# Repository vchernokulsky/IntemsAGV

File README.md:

#ROS
В репозитории находятся два рабочих пространства:

- рабочее пространства робота (для jetson nano):
`IntemsAGV/software/catkin_ws`
- рабочее пространство с симуляциями в Gazebo
`IntemsAGV/software/Simulation/catkin_ws`

Для работы с Ros в каждом терминале, находясь в корне рабочего пространства
(папка catkin_ws) необходимо выполнить команду `source devel/setup.bash`

Для распределенного запуска нод в каждом терминале необходимо указать адрес 
Ros-мастера(jetson nano, порт 11311 является стандартным): `export ROS_MASTER_URI=http://192.168.0.150:11311` 

## Custom diff drive
Управление роботом написаное нами

- осуществляет отправку данных полученных из топика /cmd_vel на робота в формате [left_dir, left_speed, right_dir,right_speed]
- на основе данных считанных с энкодера (**линейные скорости** левого и правого колеса) публикует одометрию
- публикует tf состояние робота
- публикует данные с rplidar (LaserScan) в топик /scan
- ~~публикует данные с raspbery-cam~~

Для запуска: `roslaunch cube_robot cube_robot.launch`

## diff_drive (Python)
Сделано на основе https://github.com/merose/diff_drive

- осуществляет отправку данных полученных из топика /cmd_vel на робота в формате [left_dir, left_speed, right_dir,right_speed]
- на основе данных считанных с энкодера (**кол-во тиков** на левом и правом колесе) публикует одометрию

Настрока параметров роботов осуществляется в файле `IntemsAGV/software/catkin_ws/src/diff_drive/config/params.yaml`

Для запуска: `roslaunch diff_drive diff_drive.launch`

## differential drive (c++)
**!!!требует доработки для использования с нашим роботом!!!**

пока запущен только пример

Для использования необходимо установить ros-control, ros-controllers: 

`sudo apt-get install ros-melodic-ros-control ros-melodic-ros-controllers`

Документация по ros-control: https://github.com/ros-controls/ros_control/wiki

Пример использования https://github.com/eborghi10/my_ROS_mobile_robot.git 

Для запуска примера: ` roslaunch my_robot_base hw_control.launch`

Конфигурация робота для примера: `IntemsAGV/software/catkin_ws/src/my_ROS_mobile_robot/my_robot_control/config`

- на основе /cmd_vel вычисляет линейные скорости для левого и правого колеса и публикует в топики /my_robot/right_wheel_vel и /my_robot/left_wheel_vel
- (_может быть изменено_) публикует одометрию на основе на основе угла поворота колёс (угол поворота читается из топиков /my_robot/left_wheel_angle и /my_robot/right_wheel_angle)

## Запуск отельных нод
#### публикация tf состояния робота
`roslaunch cube_robot tf.launch`
#### Rplidar
`roslaunch rplidar_ros rplidar.launch`
#### teleop (из консоли)
`roslaunch cube_robot_teleop cube_robot_teleop_key.launch`
#### teleop (из приложения android)
`roslaunch cube_robot_teleop cube_robot_teleop_server.launch`

установщик для приложения находится в папке `IntemsAGV/software/RobotController/app/release`

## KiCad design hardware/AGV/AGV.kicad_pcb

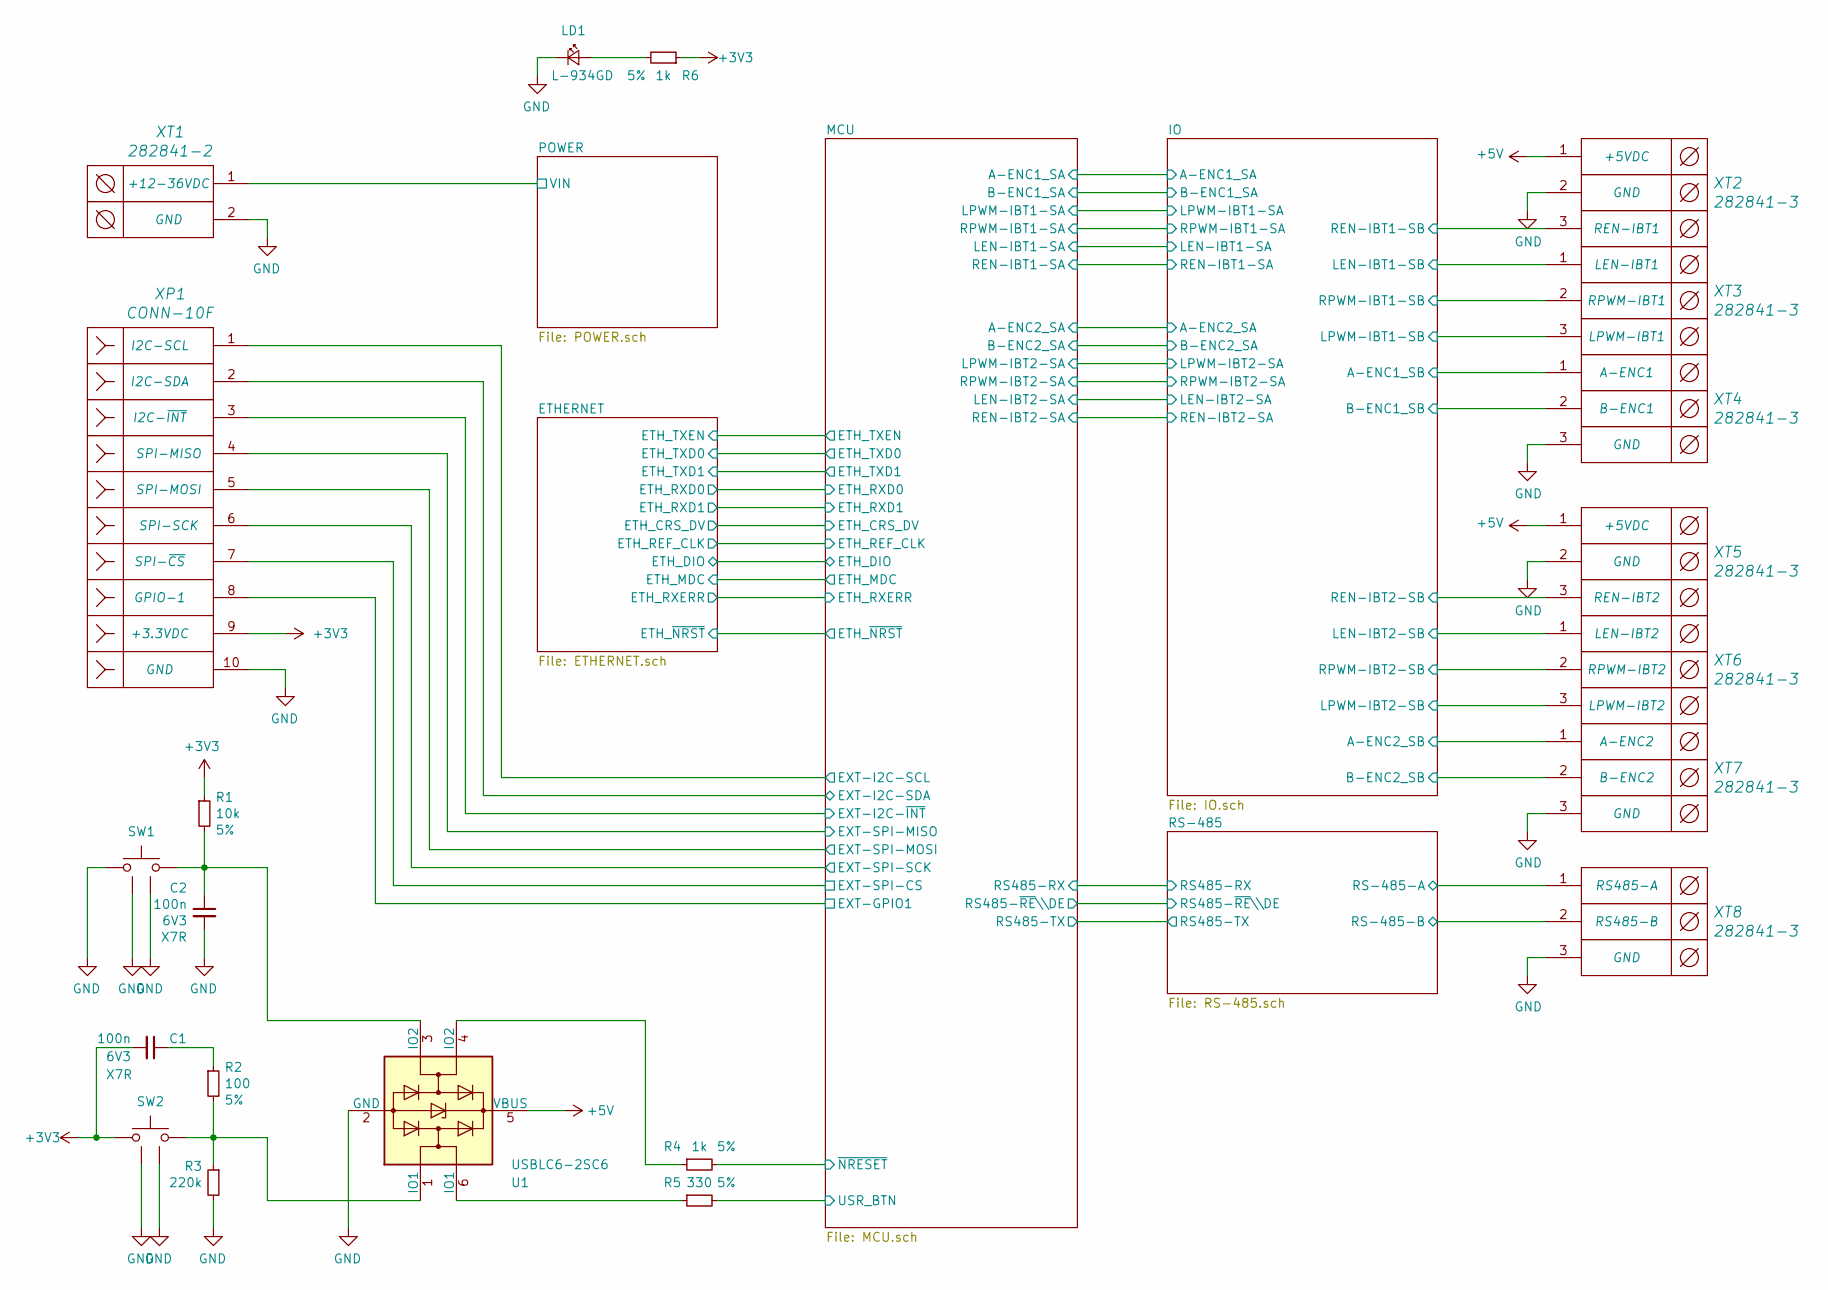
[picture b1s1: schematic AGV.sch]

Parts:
C1, C2: 100n; C_0603_1608Metric; Tolerance X7R; PartNumber CC0603KRX7R9BB104
LD1: L-934GD; LED_D3.0mm; PartNumber L-934GD
R1: 10k; R_0603_1608Metric; Tolerance 5%; PartNumber RC0603FR-0710KL
R2: 100; R_0603_1608Metric; Tolerance 5%; PartNumber RC0603FR-07100RL
R3: 220k; R_0603_1608Metric; Tolerance Tolerance; PartNumber RC0603FR-07200KL
R4, R6: 1k; R_0603_1608Metric; Tolerance 5%; PartNumber CRCW06031K00FKEA
R5: 330; R_0603_1608Metric; Tolerance 5%; PartNumber RC0603FR-07330RL
SW1, SW2: 1-1825027-7; PartNumber 1-1825027-7
U1: USBLC6-2SC6; SOT-23-6; PartNumber USBLC6-2SC6
XP1: CONN-10F; PinSocket_1x10_P2.54mm_Vertical; PartNumber PBS-10
XT1: 282841-2; PartNumber 282841-2
XT2, XT3, XT4, XT5, XT6, XT7, XT8: 282841-3; PartNumber 282841-3

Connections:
+3V3: C1.2, R1.1, R6.1, SW2.2, XP1.9; also elsewhere on the board
+5V: U1.5 (VBUS), XT2.1, XT5.1; also elsewhere on the board
/IO/A-ENC1_SB: XT4.1; also elsewhere on the board
/IO/A-ENC2_SB: XT7.1; also elsewhere on the board
/IO/B-ENC1_SB: XT4.2; also elsewhere on the board
/IO/B-ENC2_SB: XT7.2; also elsewhere on the board
/IO/LEN-IBT1-SB: XT3.1; also elsewhere on the board
/IO/LEN-IBT2-SB: XT6.1; also elsewhere on the board
/IO/LPWM-IBT1-SB: XT3.3; also elsewhere on the board
/IO/LPWM-IBT2-SB: XT6.3; also elsewhere on the board
/IO/REN-IBT1-SB: XT2.3; also elsewhere on the board
/IO/REN-IBT2-SB: XT5.3; also elsewhere on the board
/IO/RPWM-IBT1-SB: XT3.2; also elsewhere on the board
/IO/RPWM-IBT2-SB: XT6.2; also elsewhere on the board
/MCU/EXT-GPIO1: XP1.8; also elsewhere on the board
/MCU/EXT-I2C-SCL: XP1.1; also elsewhere on the board
/MCU/EXT-I2C-SDA: XP1.2; also elsewhere on the board
/MCU/EXT-I2C-~INT: XP1.3; also elsewhere on the board
/MCU/EXT-SPI-CS: XP1.7; also elsewhere on the board
/MCU/EXT-SPI-MISO: XP1.4; also elsewhere on the board
/MCU/EXT-SPI-MOSI: XP1.5; also elsewhere on the board
/MCU/EXT-SPI-SCK: XP1.6; also elsewhere on the board
/MCU/USR_BTN: R5.2; also elsewhere on the board
/MCU/~NRESET: R4.2; also elsewhere on the board
/POWER/VIN: XT1.1; also elsewhere on the board
/RS-485/RS-485-A: XT8.1; also elsewhere on the board
/RS-485/RS-485-B: XT8.2; also elsewhere on the board
GND: C2.2, LD1.1 (K), R3.2, SW1.2, SW1.3 (shield), SW1.4 (shield), SW2.3 (shield), SW2.4 (shield), U1.2 (GND), XP1.10, XT1.2, XT2.2, XT4.3, XT5.2, XT7.3, XT8.3; also elsewhere on the board
unnamed: C1.1, R2.1
unnamed: C2.1, R1.2, SW1.1, U1.3 (IO2)
unnamed: LD1.2 (A), R6.2
unnamed: R2.2, R3.1, SW2.1, U1.1 (IO1)
unnamed: R4.1, U1.4 (IO2)
unnamed: R5.1, U1.6 (IO1)

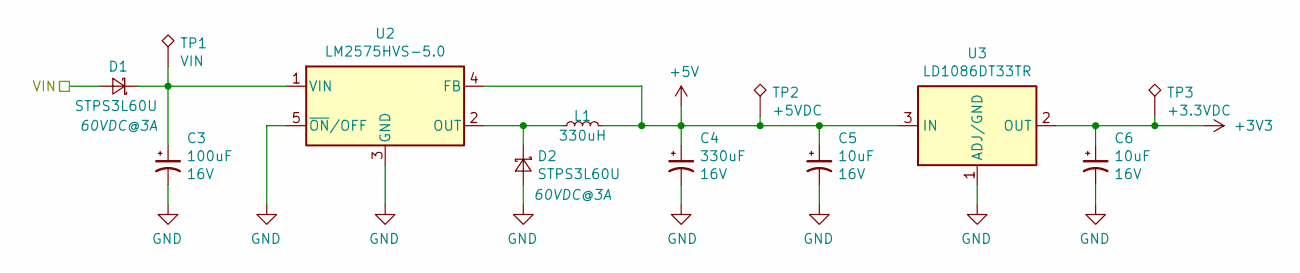
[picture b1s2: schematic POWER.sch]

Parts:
C3: 100uF; CP_Elec_10x10.5; PartNumber JCK1H101M100105
C4: 330uF; CP_Elec_10x10.5; PartNumber JCK1E331M100105
C5, C6: 10uF; CP_Elec_4x5.4; PartNumber JCK1C100M040054
D1, D2: STPS3L60U; D_SMB; PartNumber STPS3L60U
L1: 330uH; CDRH127; PartNumber CDRH127/LDNP-331MC
TP1: VIN; TestPoint_Pad_1.5x1.5mm
TP2: +5VDC; TestPoint_Pad_1.5x1.5mm
TP3: +3.3VDC; TestPoint_Pad_1.5x1.5mm
U2: LM2575HVS-5.0; TO-263-5Lead; PartNumber LM2575HVS-5.0
U3: LD1086DT33TR; TO-252-2; PartNumber LD1086DT33TR

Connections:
+3V3: C6.1, TP3.1, U3.2 (OUT); also elsewhere on the board
+5V: C4.1, C5.1, L1.2, TP2.1, U2.4 (FB), U3.3 (IN); also elsewhere on the board
/POWER/VIN: D1.2 (A); also elsewhere on the board
GND: C3.2, C4.2, C5.2, C6.2, D2.2 (A), U2.3 (GND), U2.5 (~ON~/OFF), U3.1 (ADJ/GND); also elsewhere on the board
unnamed: C3.1, D1.1 (K), TP1.1, U2.1 (VIN)
unnamed: D2.1 (K), L1.1, U2.2 (OUT)

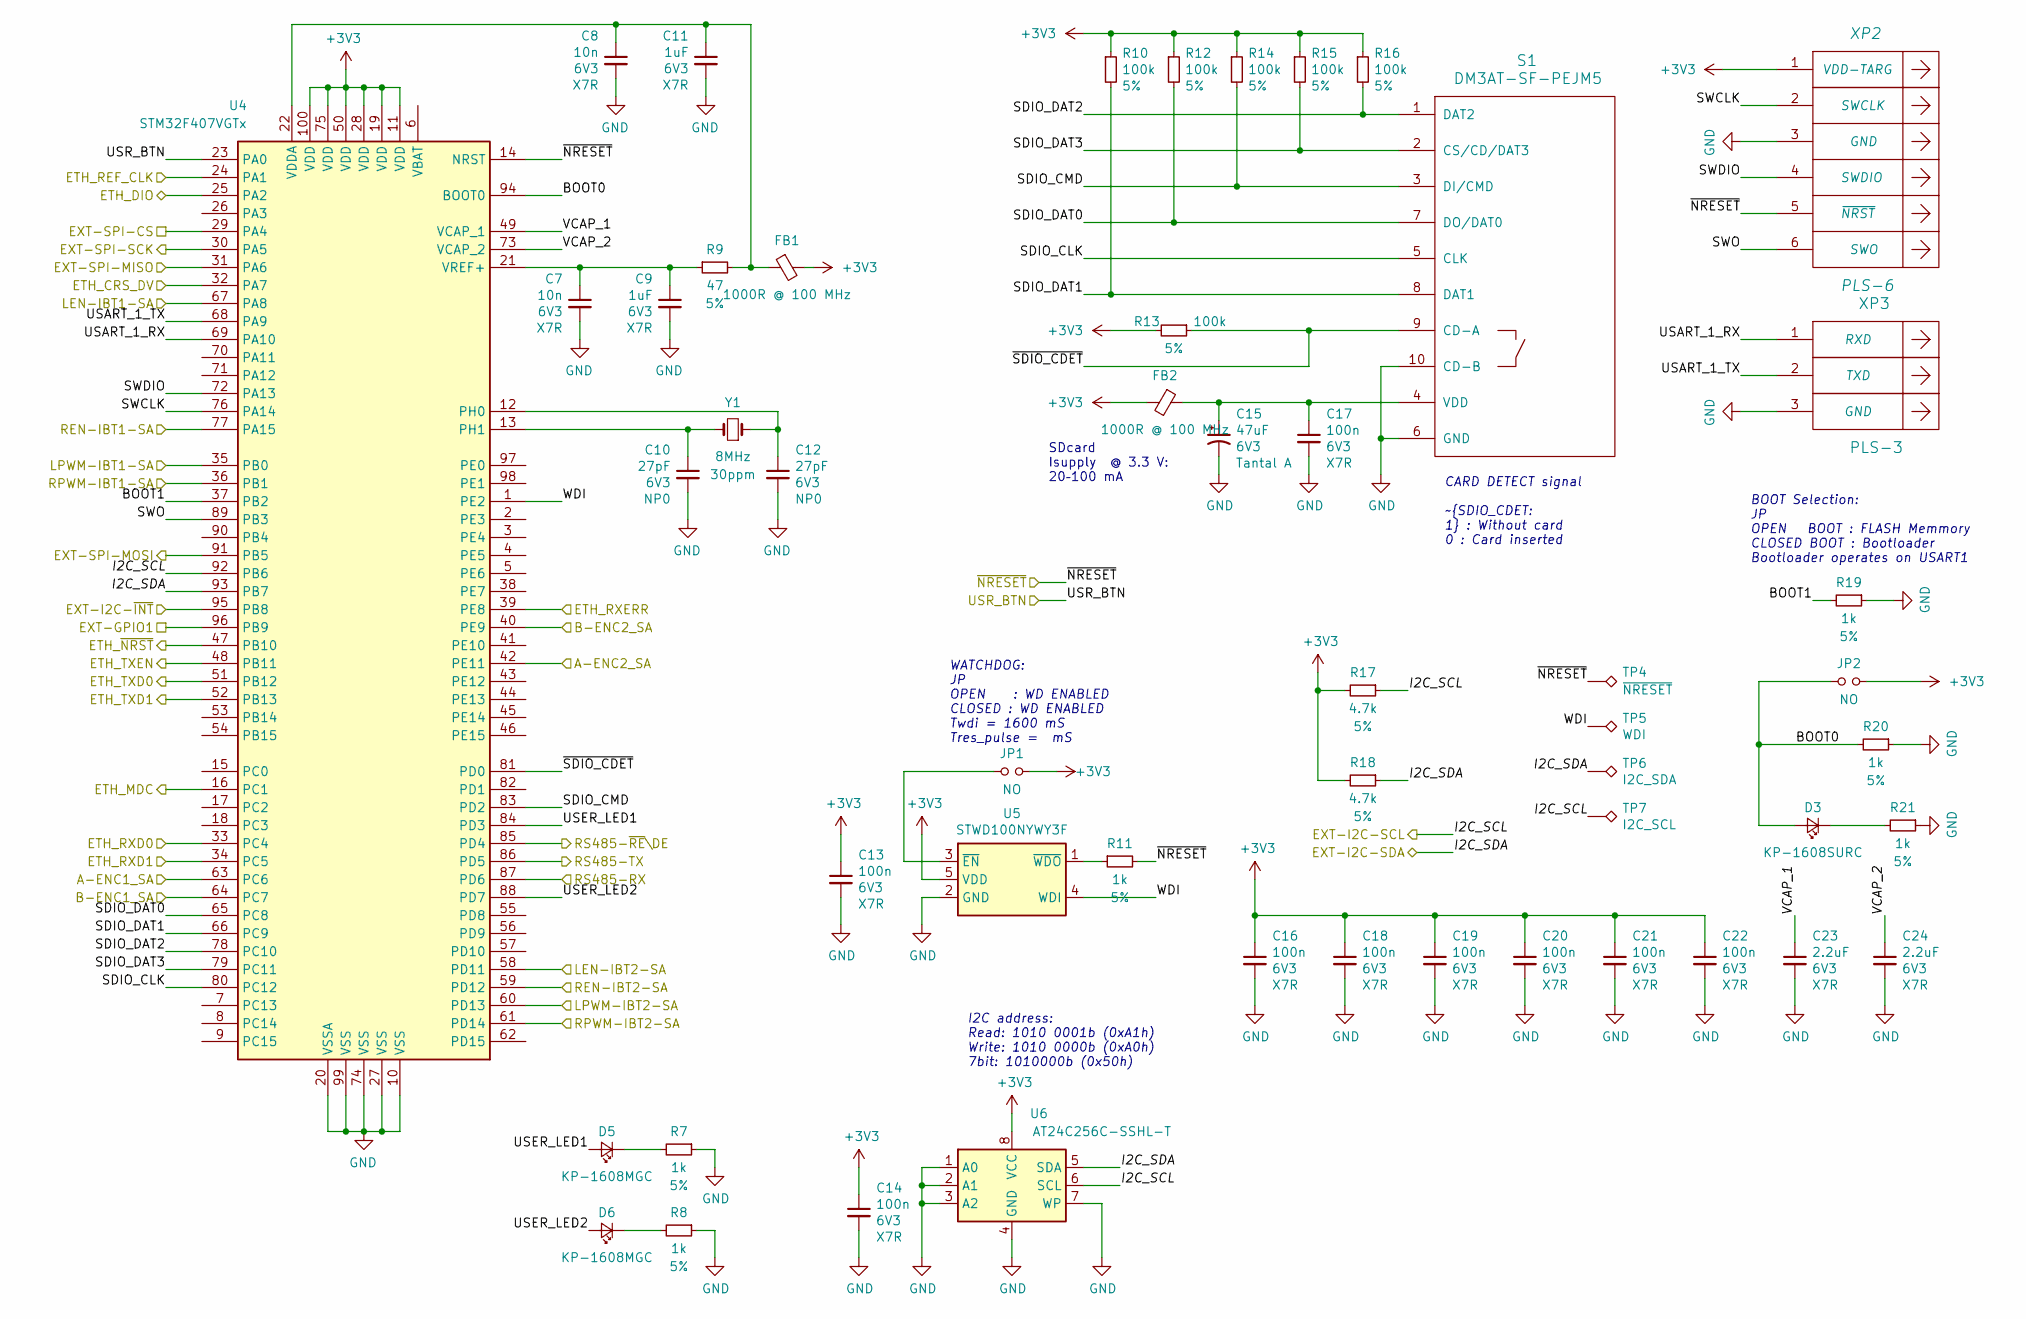
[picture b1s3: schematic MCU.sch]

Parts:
C7, C8: 10n; C_0603_1608Metric; Tolerance X7R; PartNumber CC0603KRX7R9BB103
C9, C11: 1uF; C_0603_1608Metric; Tolerance X7R; PartNumber GRM188R71C105KA12D
C10, C12: 27pF; C_0603_1608Metric; Tolerance NP0; PartNumber CC0603JRNPO9BN270
C13, C14, C16, C17, C18, C19, C20, C21, C22: 100n; C_0603_1608Metric; Tolerance X7R; PartNumber CC0603KRX7R9BB104
C15: 47uF; TantalSizeA; Tolerance Tantal A; PartNumber 293D476X96R3A2TE3
C23, C24: 2.2uF; C_0603_1608Metric; Tolerance X7R; PartNumber GRM188R71A225KE15D
D3: KP-1608SURC; LED_0603_1608Metric; PartNumber KP-1608SURC
D5, D6: KP-1608MGC; LED_0603_1608Metric; PartNumber KP-1608MGC
FB1, FB2: 1000R @ 100 MHz; L_0603_1608Metric; PartNumber BLM18AG102SN1D
JP1, JP2: NO; PinHeader_1x02_P2.54mm_Vertical; PartNumber PLS-2
R7, R8, R11, R19, R20, R21: 1k; R_0603_1608Metric; Tolerance 5%; PartNumber CRCW06031K00FKEA
R9: 47; R_0603_1608Metric; Tolerance 5%; PartNumber RC0603JR-0747RL
R10, R12, R13, R14, R15, R16: 100k; R_0603_1608Metric; Tolerance 5%; PartNumber RC0603JR-07100KL
R17, R18: 4.7k; R_0603_1608Metric; Tolerance 5%; PartNumber RC0603JR-074K7L
S1: DM3AT-SF-PEJM5; PartNumber DM3AT-SF-PEJM5
TP4: ~NRESET; TestPoint_Pad_1.5x1.5mm
TP5: WDI; TestPoint_THTPad_2.0x2.0mm_Drill1.0mm
TP6: I2C_SDA; TestPoint_THTPad_2.0x2.0mm_Drill1.0mm
TP7: I2C_SCL; TestPoint_THTPad_2.0x2.0mm_Drill1.0mm
U4: STM32F407VGTx; LQFP-100_14x14mm_P0.5mm; PartNumber STM32F407VGT6
U5: STWD100NYWY3F; SOT-23-5; PartNumber STWD100NYWY3F
U6: AT24C256C-SSHL-T; SO-8_3.9x4.9mm_P1.27mm; PartNumber M24256-BWMN6P
XP2: PLS-6; PinHeader_1x06_P2.54mm_Vertical; PartNumber PLS-6
XP3: PLS-3; PinHeader_1x03_P2.54mm_Vertical; PartNumber PLS-3
Y1: 8MHz; Crystal_SMD_Abracon_ABM3-2Pin_5.0x3.2mm; Tolerance 30ppm; PartNumber ABM3-8.000MHZ-D2Y-T

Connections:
+3V3: C13.1, C14.1, C16.1, C18.1, C19.1, C20.1, C21.1, C22.1, FB1.2, FB2.2, JP1.2, JP2.2, R10.1, R12.1, R13.2, R14.1, R15.1, R16.1, R17.2, R18.2, U4.11 (VDD), U4.19 (VDD), U4.28 (VDD), U4.50 (VDD), U4.75 (VDD), U4.100 (VDD), U5.5 (VDD), U6.8 (VCC), XP2.1; also elsewhere on the board
/ETHERNET/ETH_CRS_DV: U4.32 (PA7); also elsewhere on the board
/ETHERNET/ETH_DIO: U4.25 (PA2); also elsewhere on the board
/ETHERNET/ETH_MDC: U4.16 (PC1); also elsewhere on the board
/ETHERNET/ETH_REF_CLK: U4.24 (PA1); also elsewhere on the board
/ETHERNET/ETH_RXD0: U4.33 (PC4); also elsewhere on the board
/ETHERNET/ETH_RXD1: U4.34 (PC5); also elsewhere on the board
/ETHERNET/ETH_RXERR: U4.39 (PE8); also elsewhere on the board
/ETHERNET/ETH_TXD0: U4.51 (PB12); also elsewhere on the board
/ETHERNET/ETH_TXD1: U4.52 (PB13); also elsewhere on the board
/ETHERNET/ETH_TXEN: U4.48 (PB11); also elsewhere on the board
/ETHERNET/ETH_~NRST: U4.47 (PB10); also elsewhere on the board
/IO/A-ENC1_SA: U4.63 (PC6); also elsewhere on the board
/IO/A-ENC2_SA: U4.42 (PE11); also elsewhere on the board
/IO/B-ENC1_SA: U4.64 (PC7); also elsewhere on the board
/IO/B-ENC2_SA: U4.40 (PE9); also elsewhere on the board
/IO/LEN-IBT1-SA: U4.67 (PA8); also elsewhere on the board
/IO/LEN-IBT2-SA: U4.58 (PD11); also elsewhere on the board
/IO/LPWM-IBT1-SA: U4.35 (PB0); also elsewhere on the board
/IO/LPWM-IBT2-SA: U4.60 (PD13); also elsewhere on the board
/IO/REN-IBT1-SA: U4.77 (PA15); also elsewhere on the board
/IO/REN-IBT2-SA: U4.59 (PD12); also elsewhere on the board
/IO/RPWM-IBT1-SA: U4.36 (PB1); also elsewhere on the board
/IO/RPWM-IBT2-SA: U4.61 (PD14); also elsewhere on the board
/MCU/BOOT0: D3.2 (A), JP2.1, R20.2, U4.94 (BOOT0)
/MCU/BOOT1: R19.2, U4.37 (PB2)
/MCU/EXT-GPIO1: U4.96 (PB9); also elsewhere on the board
/MCU/EXT-I2C-SCL: R17.1, TP7.1, U4.92 (PB6), U6.6 (SCL); also elsewhere on the board
/MCU/EXT-I2C-SDA: R18.1, TP6.1, U4.93 (PB7), U6.5 (SDA); also elsewhere on the board
/MCU/EXT-I2C-~INT: U4.95 (PB8); also elsewhere on the board
/MCU/EXT-SPI-CS: U4.29 (PA4); also elsewhere on the board
/MCU/EXT-SPI-MISO: U4.31 (PA6); also elsewhere on the board
/MCU/EXT-SPI-MOSI: U4.91 (PB5); also elsewhere on the board
/MCU/EXT-SPI-SCK: U4.30 (PA5); also elsewhere on the board
/MCU/RS485-RX: U4.87 (PD6); also elsewhere on the board
/MCU/RS485-TX: U4.86 (PD5); also elsewhere on the board
/MCU/RS485-~RE~\DE: U4.85 (PD4); also elsewhere on the board
/MCU/SDIO_CLK: S1.5 (CLK), U4.80 (PC12)
/MCU/SDIO_CMD: R14.2, S1.3 (DI/CMD), U4.83 (PD2)
/MCU/SDIO_DAT0: R12.2, S1.7 (DO/DAT0), U4.65 (PC8)
/MCU/SDIO_DAT1: R10.2, S1.8 (DAT1), U4.66 (PC9)
/MCU/SDIO_DAT2: R16.2, S1.1 (DAT2), U4.78 (PC10)
/MCU/SDIO_DAT3: R15.2, S1.2 (CS/CD/DAT3), U4.79 (PC11)
/MCU/SWCLK: U4.76 (PA14), XP2.2
/MCU/SWDIO: U4.72 (PA13), XP2.4
/MCU/SWO: U4.89 (PB3), XP2.6
/MCU/USART_1_RX: U4.69 (PA10), XP3.1
/MCU/USART_1_TX: U4.68 (PA9), XP3.2
/MCU/USER_LED1: D5.2 (A), U4.84 (PD3)
/MCU/USER_LED2: D6.2 (A), U4.88 (PD7)
/MCU/USR_BTN: U4.23 (PA0); also elsewhere on the board
/MCU/VCAP_1: C23.1, U4.49 (VCAP_1)
/MCU/VCAP_2: C24.1, U4.73 (VCAP_2)
/MCU/WDI: TP5.1, U4.1 (PE2), U5.4 (WDI)
/MCU/~NRESET: R11.2, TP4.1, U4.14 (NRST), XP2.5; also elsewhere on the board
/MCU/~SDIO_CDET: R13.1, S1.9 (CD-A), U4.81 (PD0)
GND: C7.2, C8.2, C9.2, C10.2, C11.2, C12.2, C13.2, C14.2, C15.2, C16.2, C17.2, C18.2, C19.2, C20.2, C21.2, C22.2, C23.2, C24.2, R7.1, R8.1, R19.1, R20.1, R21.1, S1.6 (GND), S1.10 (CD-B), U4.10 (VSS), U4.20 (VSSA), U4.27 (VSS), U4.74 (VSS), U4.99 (VSS), U5.2 (GND), U6.1 (A0), U6.2 (A1), U6.3 (A2), U6.4 (GND), U6.7 (WP), XP2.3, XP3.3; also elsewhere on the board
unnamed: C7.1, C9.1, R9.1, U4.21 (VREF+)
unnamed: C10.1, U4.13 (PH1), Y1.2
unnamed: C8.1, C11.1, FB1.1, R9.2, U4.22 (VDDA)
unnamed: C12.1, U4.12 (PH0), Y1.1
unnamed: C15.1, C17.1, FB2.1, S1.4 (VDD)
unnamed: D3.1 (K), R21.2
unnamed: D5.1 (K), R7.2
unnamed: D6.1 (K), R8.2
unnamed: JP1.1, U5.3 (~EN)
unnamed: R11.1, U5.1 (~WDO)

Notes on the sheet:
I2C address: Read: 1010 0001b (0xA1h) Write: 1010 0000b (0xA0h) 7bit: 1010000b (0x50h)
BOOT Selection: JP OPEN BOOT : FLASH Memmory CLOSED BOOT : Bootloader Bootloader operates on USART1
SDcard Isupply @ 3.3 V: 20–100 mA
CARD DETECT signal ~SDIO_CDET: 1 : Without card 0 : Card inserted
WATCHDOG: JP OPEN : WD ENABLED CLOSED : WD ENABLED Twdi = 1600 mS Tres_pulse = mS

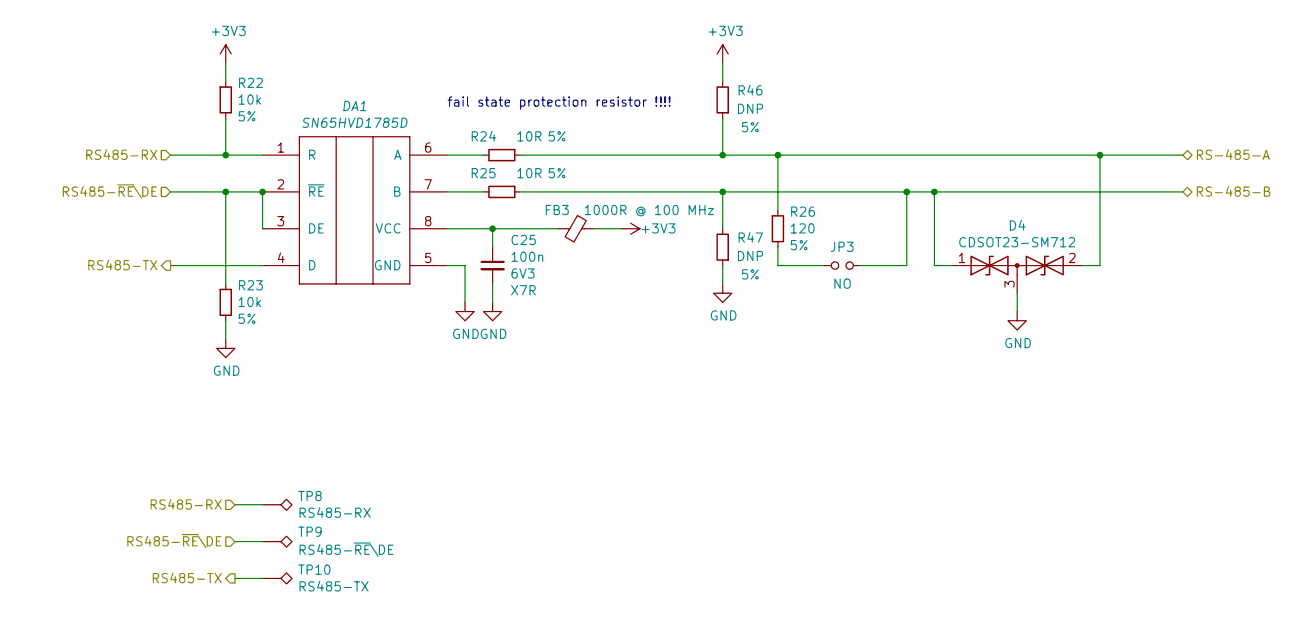
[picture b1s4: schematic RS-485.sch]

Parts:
C25: 100n; C_0603_1608Metric; Tolerance X7R; PartNumber CC0603KRX7R9BB104
D4: CDSOT23-SM712; SOT-23; PartNumber CDSOT23-SM712
DA1: SN65HVD1785D; SO-8_3.9x4.9mm_P1.27mm; PartNumber SN65HVD1785D
FB3: 1000R @ 100 MHz; L_0603_1608Metric; PartNumber BLM18AG102SN1D
JP3: NO; PinHeader_1x02_P2.54mm_Vertical; PartNumber PLS-2
R22, R23: 10k; R_0603_1608Metric; Tolerance 5%; PartNumber RC0603FR-0710KL
R24, R25: 10R; R_0603_1608Metric; Tolerance 5%; PartNumber RC0603JR-0710RL
R26: 120; R_0805_2012Metric; Tolerance 5%; PartNumber RC0805FR-07120RL
R46, R47: DNP; R_0603_1608Metric; Tolerance 5%; PartNumber RC0603JR-0710RL
TP8: RS485-RX; TestPoint_THTPad_2.0x2.0mm_Drill1.0mm
TP9: RS485-~RE~\\DE; TestPoint_THTPad_2.0x2.0mm_Drill1.0mm
TP10: RS485-TX; TestPoint_THTPad_2.0x2.0mm_Drill1.0mm

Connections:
+3V3: FB3.1, R22.1, R46.2; also elsewhere on the board
/MCU/RS485-RX: DA1.1 (R), R22.2, TP8.1; also elsewhere on the board
/MCU/RS485-TX: DA1.4 (D), TP10.1; also elsewhere on the board
/MCU/RS485-~RE~\DE: DA1.2 (~RE), DA1.3 (DE), R23.1, TP9.1; also elsewhere on the board
/RS-485/RS-485-A: D4.2 (A2), R24.1, R26.1, R46.1; also elsewhere on the board
/RS-485/RS-485-B: D4.1 (A1), JP3.2, R25.1, R47.2; also elsewhere on the board
GND: C25.2, D4.3 (common), DA1.5 (GND), R23.2, R47.1; also elsewhere on the board
unnamed: C25.1, DA1.8 (VCC), FB3.2
unnamed: DA1.6 (A), R24.2
unnamed: DA1.7 (B), R25.2
unnamed: JP3.1, R26.2

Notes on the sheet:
fail state protection resistor !!!!

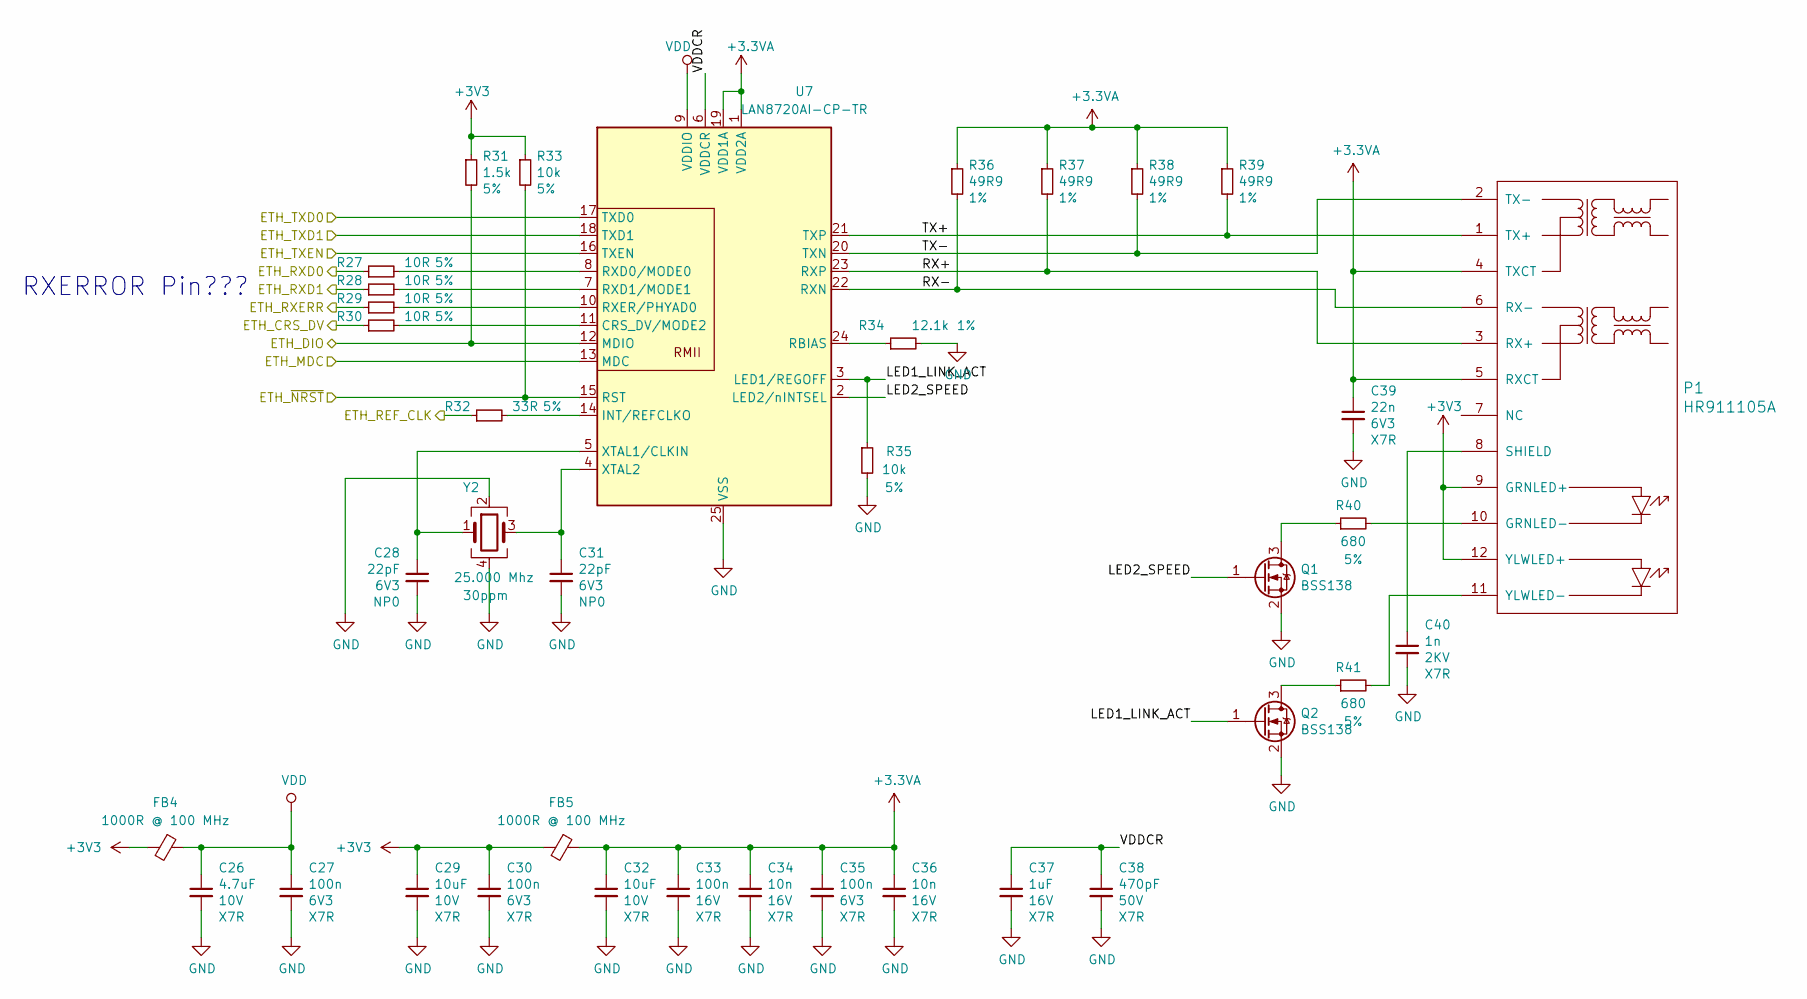
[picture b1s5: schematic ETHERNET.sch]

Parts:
C26: 4.7uF; C_0603_1608Metric; Tolerance X7R; PartNumber CC0603KRX5R6BB475
C27, C30, C33, C35: 100n; C_0603_1608Metric; Tolerance X7R; PartNumber CC0603KRX7R9BB104
C28, C31: 22pF; C_0603_1608Metric; Tolerance NP0; PartNumber GRM1885C1H220JA01D
C29, C32: 10uF; C_0603_1608Metric; Tolerance X7R; PartNumber CC0603KRX5R6BB106
C34, C36: 10n; C_0603_1608Metric; Tolerance X7R; PartNumber CC0603KRX7R9BB103
C37: 1uF; C_0603_1608Metric; Tolerance X7R; PartNumber GRM188R71C105KA12D
C38: 470pF; C_0603_1608Metric; Tolerance X7R; PartNumber GRM188R71H471KA01D
C39: 22n; C_0603_1608Metric; Tolerance X7R; PartNumber CC0603KRX7R9BB223
C40: 1n; C_1206_3216Metric; Tolerance X7R; PartNumber CC1206KKX7RDBB102
FB4, FB5: 1000R @ 100 MHz; L_0603_1608Metric; PartNumber BLM18AG102SN1D
P1: HR911105A; HR911105; PartNumber HR911105A
Q1, Q2: BSS138; SOT-23; PartNumber BSS138-7-F
R27, R28, R29, R30: 10R; R_0603_1608Metric; Tolerance 5%; PartNumber RC0603JR-0710RL
R31: 1.5k; R_0603_1608Metric; Tolerance 5%; PartNumber RC0603JR-071K5L
R32: 33R; R_0603_1608Metric; Tolerance 5%; PartNumber RC0603FR-0733RL
R33, R35: 10k; R_0603_1608Metric; Tolerance 5%; PartNumber RC0603FR-0710KL
R34: 12.1k; R_0603_1608Metric; Tolerance 1%; PartNumber RC0603FR-0712K1L
R36, R37, R38, R39: 49R9; R_0603_1608Metric; Tolerance 1%; PartNumber RC0603FR-0749R9L
R40, R41: 680; R_0603_1608Metric; Tolerance 5%; PartNumber RC0805FR-07680RL
U7: LAN8720AI-CP-TR; QFN-24-1EP_4x4mm_P0.5mm_EP2.6x2.6mm_ThermalVias; PartNumber LAN8720AI-CP-TR
Y2: 25.000 Mhz; Crystal_SMD_Geyer_KX-7T-4Pin_3.2x2.5mm; Tolerance 30ppm; PartNumber KX-7 25.0 MHz

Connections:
+3.3VA: C32.1, C33.1, C34.1, C35.1, C36.1, C39.1, FB5.1, P1.4 (TXCT), P1.5 (RXCT), R36.1, R37.1, R38.1, R39.1, U7.1 (VDD2A), U7.19 (VDD1A)
+3V3: C29.1, C30.1, FB4.2, FB5.2, P1.9 (GRNLED+), P1.12 (YLWLED+), R31.1, R33.1; also elsewhere on the board
/ETHERNET/ETH_CRS_DV: R30.1; also elsewhere on the board
/ETHERNET/ETH_DIO: R31.2, U7.12 (MDIO); also elsewhere on the board
/ETHERNET/ETH_MDC: U7.13 (MDC); also elsewhere on the board
/ETHERNET/ETH_REF_CLK: R32.1; also elsewhere on the board
/ETHERNET/ETH_RXD0: R27.1; also elsewhere on the board
/ETHERNET/ETH_RXD1: R28.1; also elsewhere on the board
/ETHERNET/ETH_RXERR: R29.1; also elsewhere on the board
/ETHERNET/ETH_TXD0: U7.17 (TXD0); also elsewhere on the board
/ETHERNET/ETH_TXD1: U7.18 (TXD1); also elsewhere on the board
/ETHERNET/ETH_TXEN: U7.16 (TXEN); also elsewhere on the board
/ETHERNET/ETH_~NRST: R33.2, U7.15 (RST); also elsewhere on the board
/ETHERNET/LED1_LINK_ACT: Q2.1 (G), R35.1, U7.3 (LED1/REGOFF)
/ETHERNET/LED2_SPEED: Q1.1 (G), U7.2 (LED2/nINTSEL)
/ETHERNET/RX+: P1.3 (RX+), R37.2, U7.23 (RXP)
/ETHERNET/RX-: P1.6 (RX-), R36.2, U7.22 (RXN)
/ETHERNET/TX+: P1.1 (TX+), R39.2, U7.21 (TXP)
/ETHERNET/TX-: P1.2 (TX-), R38.2, U7.20 (TXN)
/ETHERNET/VDDCR: C37.1, C38.1, U7.6 (VDDCR)
GND: C26.2, C27.2, C28.2, C29.2, C30.2, C31.2, C32.2, C33.2, C34.2, C35.2, C36.2, C37.2, C38.2, C39.2, C40.2, Q1.2 (S), Q2.2 (S), R34.2, R35.2, U7.25 (VSS), Y2.2, Y2.4; also elsewhere on the board
unnamed: C28.1, U7.5 (XTAL1/CLKIN), Y2.1
unnamed: C31.1, U7.4 (XTAL2), Y2.3
unnamed: C40.1, P1.8 (SHIELD)
unnamed: P1.10 (GRNLED-), R40.2
unnamed: P1.11 (YLWLED-), R41.2
unnamed: Q1.3 (D), R40.1
unnamed: Q2.3 (D), R41.1
unnamed: R27.2, U7.8 (RXD0/MODE0)
unnamed: R28.2, U7.7 (RXD1/MODE1)
unnamed: R29.2, U7.10 (RXER/PHYAD0)
unnamed: R30.2, U7.11 (CRS_DV/MODE2)
unnamed: R32.2, U7.14 (INT/REFCLKO)
unnamed: R34.1, U7.24 (RBIAS)
VDD: C26.1, C27.1, FB4.1, U7.9 (VDDIO)

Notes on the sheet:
RXERROR Pin???

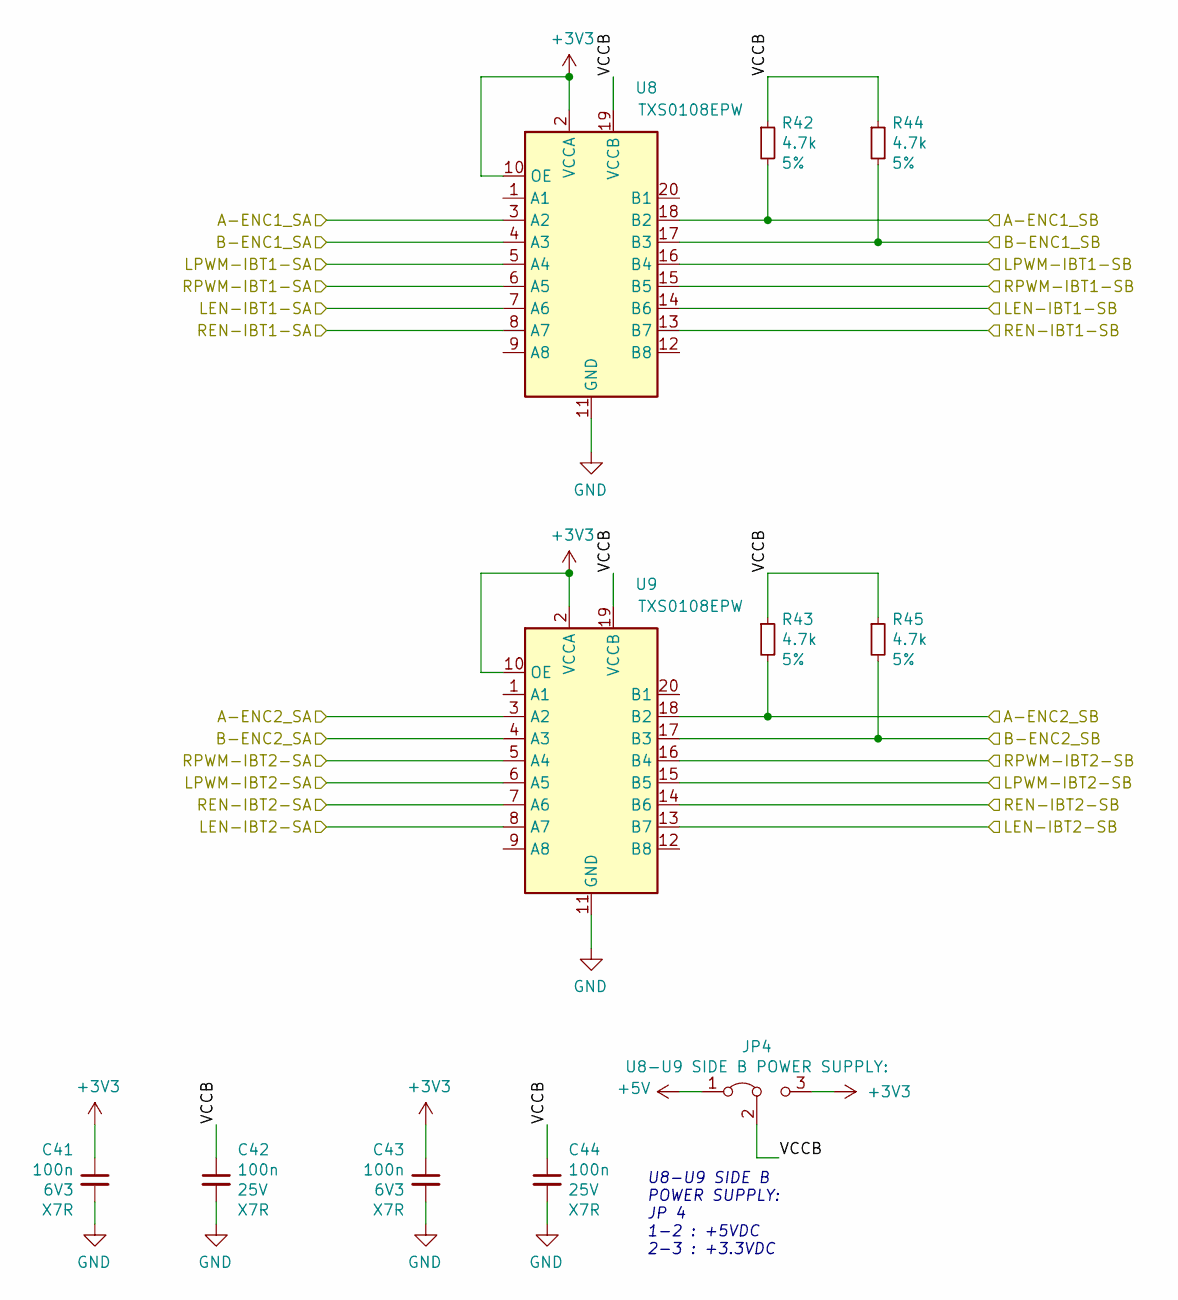
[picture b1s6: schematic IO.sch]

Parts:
C41, C42, C43, C44: 100n; C_0603_1608Metric; Tolerance X7R; PartNumber CC0603KRX7R9BB104
JP4: U8-U9 SIDE B POWER SUPPLY:; PinHeader_1x03_P2.54mm_Vertical; PartNumber PLS-3
R42, R43, R44, R45: 4.7k; R_0603_1608Metric; Tolerance 5%; PartNumber RC0603JR-074K7L
U8, U9: TXS0108EPW; TSSOP-20-P0.65-W6.5mm-H4.4mm-IPC7351-S-B; PartNumber TXS0108EPW

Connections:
+3V3: C41.1, C43.1, JP4.3 (B), U8.2 (VCCA), U8.10 (OE), U9.2 (VCCA), U9.10 (OE); also elsewhere on the board
+5V: JP4.1 (A); also elsewhere on the board
/IO/A-ENC1_SA: U8.3 (A2); also elsewhere on the board
/IO/A-ENC1_SB: R42.2, U8.18 (B2); also elsewhere on the board
/IO/A-ENC2_SA: U9.3 (A2); also elsewhere on the board
/IO/A-ENC2_SB: R43.2, U9.18 (B2); also elsewhere on the board
/IO/B-ENC1_SA: U8.4 (A3); also elsewhere on the board
/IO/B-ENC1_SB: R44.2, U8.17 (B3); also elsewhere on the board
/IO/B-ENC2_SA: U9.4 (A3); also elsewhere on the board
/IO/B-ENC2_SB: R45.2, U9.17 (B3); also elsewhere on the board
/IO/LEN-IBT1-SA: U8.7 (A6); also elsewhere on the board
/IO/LEN-IBT1-SB: U8.14 (B6); also elsewhere on the board
/IO/LEN-IBT2-SA: U9.8 (A7); also elsewhere on the board
/IO/LEN-IBT2-SB: U9.13 (B7); also elsewhere on the board
/IO/LPWM-IBT1-SA: U8.5 (A4); also elsewhere on the board
/IO/LPWM-IBT1-SB: U8.16 (B4); also elsewhere on the board
/IO/LPWM-IBT2-SA: U9.6 (A5); also elsewhere on the board
/IO/LPWM-IBT2-SB: U9.15 (B5); also elsewhere on the board
/IO/REN-IBT1-SA: U8.8 (A7); also elsewhere on the board
/IO/REN-IBT1-SB: U8.13 (B7); also elsewhere on the board
/IO/REN-IBT2-SA: U9.7 (A6); also elsewhere on the board
/IO/REN-IBT2-SB: U9.14 (B6); also elsewhere on the board
/IO/RPWM-IBT1-SA: U8.6 (A5); also elsewhere on the board
/IO/RPWM-IBT1-SB: U8.15 (B5); also elsewhere on the board
/IO/RPWM-IBT2-SA: U9.5 (A4); also elsewhere on the board
/IO/RPWM-IBT2-SB: U9.16 (B4); also elsewhere on the board
/IO/VCCB: C42.1, C44.1, JP4.2 (C), R42.1, R43.1, R44.1, R45.1, U8.19 (VCCB), U9.19 (VCCB)
GND: C41.2, C42.2, C43.2, C44.2, U8.11 (GND), U9.11 (GND); also elsewhere on the board

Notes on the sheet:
U8-U9 SIDE B POWER SUPPLY: JP 4 1-2 : +5VDC 2-3 : +3.3VDC

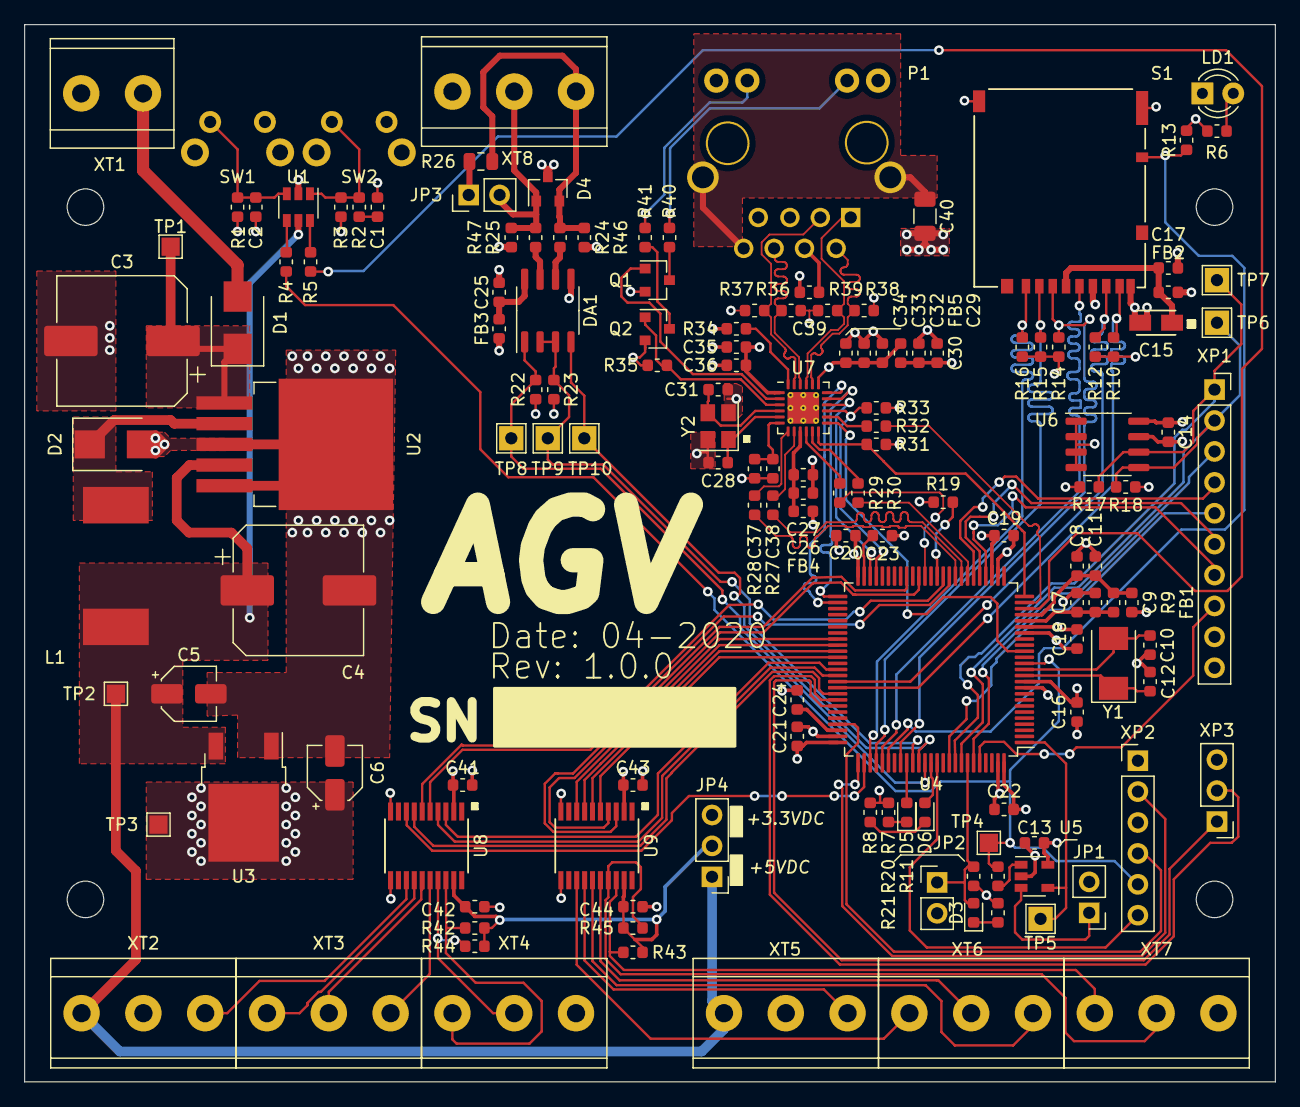
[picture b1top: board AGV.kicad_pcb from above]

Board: 4 copper layers, 102.8 x 86.9 mm, 147 parts (0 on the bottom side), 118 nets.
